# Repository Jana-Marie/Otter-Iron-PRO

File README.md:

# Otter-Iron-PRO

USB-PD soldering station for JBC C245 handles based on the [Otter-Iron](https://github.com/Jana-Marie/Otter-Iron).

 - v1.0 tested, works but not great
 - v1.1 untested, wont be tested
 - v2.0 tested, kinda works, could be much more stable

## Firmware

 - Requests and configures for USB-PD profile of 30 W or 80 W (allows variable).
 - Current limit automatically set based on PD profile available.
 - Profiles can be changed in firmware and enumerated profile will show at start up.
 - Prevents MOSFET driving if no/incompatiable USB-PD profile is advertised; allows setup/flashing with standard USB port.

## v2.0

## v1.0

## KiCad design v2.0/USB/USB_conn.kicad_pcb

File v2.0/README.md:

[BOM](https://github.com/jeanthom/Otter-Iron-PRO-BOM)

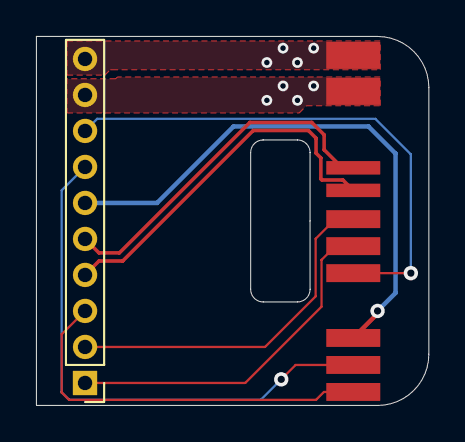
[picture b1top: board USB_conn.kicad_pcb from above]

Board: 2 copper layers, 21.8 x 20.5 mm, 11 parts (0 on the bottom side), 10 nets.

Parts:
J1: Conn_01x10; PinHeader_1x10_P2.00mm_Vertical
J2, J3: Conn_01x01; pad_1.5_3
J4, J5: Conn_01x01; pad_0.75_3
J6, J7, J8, J9, J10, J11: Conn_01x01; pad_1_2

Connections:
+3V3: J1.6, J9.1
GND: J1.10, J2.1
INT_N: J1.8, J8.1
SCL: J1.2, J6.1
SDA: J1.1, J7.1
SW1: J1.7, J10.1
SW2: J1.3, J11.1
USB_N: J1.4, J5.1
USB_P: J1.5, J4.1
VBUS: J1.9, J3.1

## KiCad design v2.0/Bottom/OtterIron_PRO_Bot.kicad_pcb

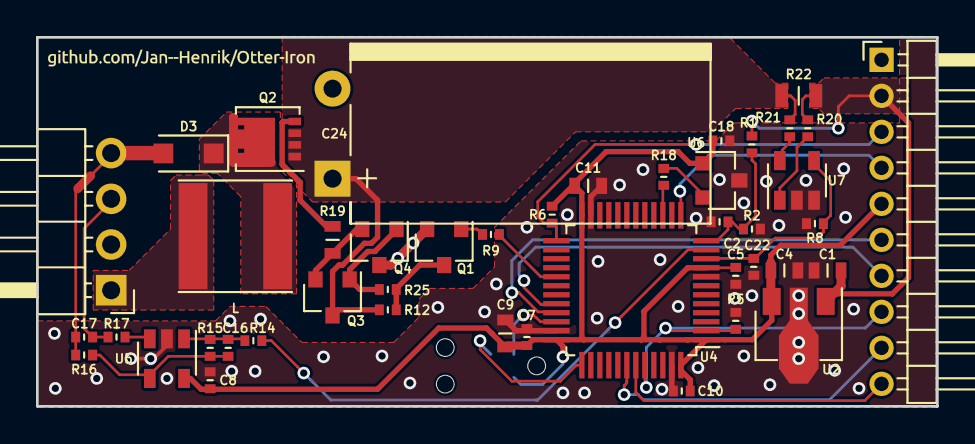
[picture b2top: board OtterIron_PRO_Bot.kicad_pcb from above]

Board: 2 copper layers, 50.0 x 20.5 mm, 46 parts (1 on the bottom side), 33 nets.

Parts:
C1, C4, C9, C11: 1μF 25V; C_0603
C2, C5, C7, C8, C10, C18, C22: 0.1μF; C_0402
C16: 18p; C_0402
C17: DNP; C_0402
C24: 1000µF; CP_Radial_D10.0mm_P5.00mm_flat
D3: B140-E3; D_SOD-123F
J1: Conn_01x10; PinHeader_1x10_P2.00mm_Horizontal
J3: C245; PinHeader_1x04_P2.54mm_Horizontal
L: 4.7u; L_Taiyo-Yuden_NR-60xx
NT1: JUNC_N; NetTie-2_SMD_Pad0.5mm
P1: TC2030-CTX; TC2030
Q1, Q3: SS8050; SOT-23
Q2: DMP3017SFG; Diodes_PowerDI3333-8
Q4: BC807; SOT-23
R1: 560k; R_0402
R2, R17: 100k; R_0402
R5, R6, R8, R9, R12, R14, R16, R18, R25: 2k37; R_0402
R15: 750k; R_0402
R19: 20; R_0603
R20, R21: 33; R_0402
R22: 10m; R_0805
U2: AP2204R-3.3; SOT-89-3
U4: STM32F072C8Tx; LQFP-48_7x7mm_P0.5mm
U5: OPA340NA; SOT-23-5
U6: MCP9700AT-ETT; SOT-23
U7: SI8540; SOT-23-5

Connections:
+3V3: C4.1, C5.1, C7.1, C8.1, C9.1, C10.1, C11.1, C18.1, J1.5, P1.1, R6.2, U2.3, U4.1, U4.9, U4.24, U4.36, U4.48, U5.5, U6.1
C245_JUNC: C17.2, J3.3, R17.1
GND: C1.2, C2.2, C4.2, C5.2, C7.2, C8.2, C9.2, C10.2, C11.2, C18.2, C22.2, C24.2, D3.2, J1.1, J3.4, NT1.2, P1.5, Q1.2, Q4.3, R2.2, R5.1, R8.2, U2.2, U4.8, U4.23, U4.35, U4.47, U5.2, U6.3, U7.2, U7.3
IIN: C22.1, R8.1, U4.10, U7.4
INT_N: J1.3, R6.1, U4.25
unnamed: C16.1, R15.1, R16.2, U5.4
unnamed: C16.2, R14.1, R15.2, U5.1
unnamed: C17.1, NT1.1, R16.1
unnamed: C24.1, Q2.1, Q2.2, Q2.3, Q3.3, R12.1, R21.2, R22.2
unnamed: D3.1, L.1, Q2.5
unnamed: J3.1, L.2
unnamed: Q1.1, R9.2
unnamed: Q1.3, R12.2, R25.1
unnamed: Q2.4, R19.2
unnamed: Q3.1, Q4.1, R25.2
unnamed: Q3.2, Q4.2, R19.1
unnamed: R17.2, U5.3
unnamed: R18.2, U6.2
unnamed: R20.2, U7.1
unnamed: R21.1, U7.5
OLED_SCL: J1.9, U4.42
OLED_SDA: J1.10, U4.43
PWM: R9.1, U4.29
SW1: J1.4, U4.13
SW2: J1.8, R5.2, U4.2, U4.44
SWCLK: P1.4, U4.37
SWDIO: P1.2, U4.34
TREF: R18.1, U4.15
TTIP: R14.2, U4.11
UIN: C2.1, R1.2, R2.1, U4.12
USB_N: J1.7, U4.32
USB_P: J1.6, U4.33
VBUS: C1.1, J1.2, R1.1, R20.1, R22.1, U2.1

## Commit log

2020-04-15 added gitignore
2020-04-15 added 3D files
2020-04-15 added images
2020-04-15 added v1.0
2020-04-17 added firmwar
2020-04-17 added pdf
2020-04-30 updated files
2020-04-30 fixed bugs
2020-05-07 increased PWM frequency, fixed crash bug when USB-C is plugged in first
2020-06-30 lower current limit, remove d term
2020-06-30 stusb4500 support and PD profile check
2020-06-30 i2c2 not doing anything
2020-06-30 setup PD profiles for 30 W and 80 W
    even though most USB PD adaptors will allow a device to draw the max
    advertised current, kosher ones will cut power if the profile has not
    been enumerated (Apple MacBook for example). Added initialisation of
    profiles at start up.
2020-07-01 following datasheet for display init in attempt to prevent noise at boot sometimes
2020-07-01 OLED start routine ds parity, PID tune
2020-07-01 integrator more applied for trim and current clamp hard
2020-07-01 crank up wduty faster inside ilimit
2020-07-02 PD status at boot
2020-07-02 stusb4500 driver in separate files
2020-07-02 think I've got screen working always 🤞
2020-07-02 README firmware features and remove build files
2021-02-07 Add missing 3D models
2023-11-19 fixed readme
